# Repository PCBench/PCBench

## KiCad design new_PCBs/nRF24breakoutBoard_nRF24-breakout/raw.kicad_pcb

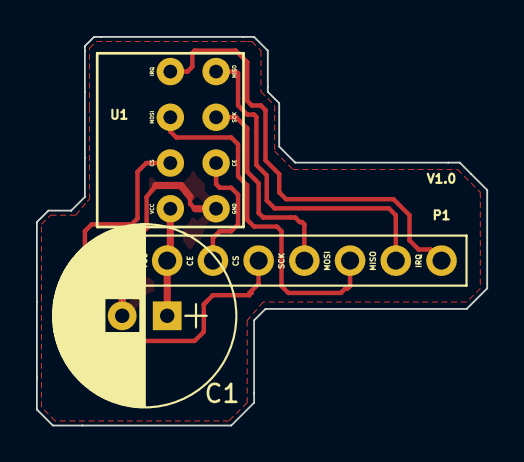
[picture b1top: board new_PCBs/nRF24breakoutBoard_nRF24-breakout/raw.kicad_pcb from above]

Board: 2 copper layers, 25.0 x 21.6 mm, 3 parts (0 on the bottom side), 8 nets.

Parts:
C1: 10uF; CP_Radial_D10.0mm_P2.50mm
P1: CONN_01X08; Pin_Header_Straight_1x08_Pitch2.54mm
U1: nRF24

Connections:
unnamed: C1.1, P1.2, U1.2
unnamed: C1.2, P1.1, U1.1
unnamed: P1.3, U1.3
unnamed: P1.4, U1.4
unnamed: P1.5, U1.5
unnamed: P1.6, U1.6
unnamed: P1.7, U1.7
unnamed: P1.8, U1.8

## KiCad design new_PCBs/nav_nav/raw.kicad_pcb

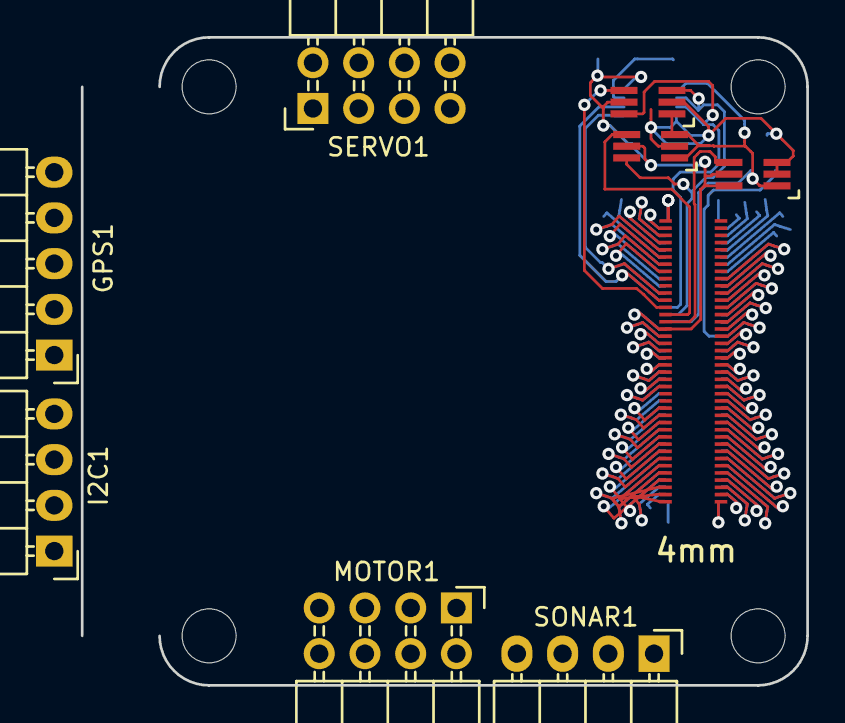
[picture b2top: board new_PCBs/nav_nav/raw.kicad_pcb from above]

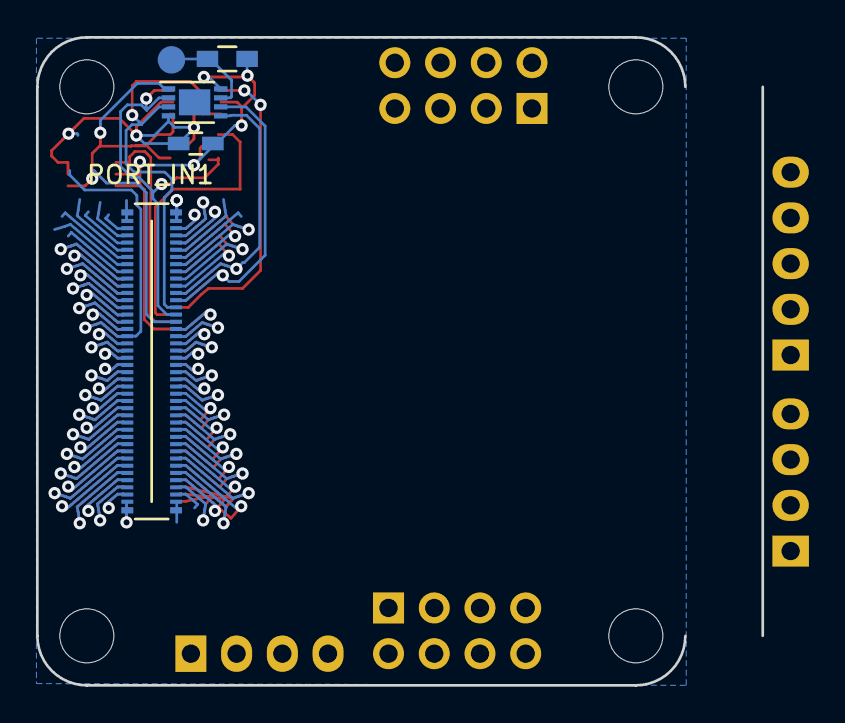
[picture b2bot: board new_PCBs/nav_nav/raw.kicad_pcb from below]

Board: 2 copper layers, 40.3 x 36.0 mm, 14 parts (5 on the bottom side), 62 nets.

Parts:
GPS1: CONN_01X05; Pin_Header_Angled_1x05
I2C1: CONN_01X04; Pin_Header_Angled_1x04
MOTOR1: CONN_02X04; Pin_Header_Angled_2x04
PORT_ANDOR1: SN74LVC1G0832; SC-70-6_Handsoldering
PORT_C1: 0.1uF; C_0603_HandSoldering
PORT_IC1: AT24CS02-MAHM; DFN-8-1EP_3x2mm_Pitch0.5mm
PORT_IN1: POLYSTACK_CONNECTOR; DF40-80pin-Header
PORT_INV1: SN74LVC1G58; SC-70-6_Handsoldering
PORT_OUT1: POLYSTACK_CONNECTOR; DF40-3-4mm-80pin-Receptacle
PORT_P1: CONN_01X01; Measurement_Point_Round-SMD-Pad_Small
PORT_R1: 10k; R_0603_HandSoldering
PORT_XOR1: SN74LVC1G58; SC-70-6_Handsoldering
SERVO1: CONN_02X04; Pin_Header_Angled_2x04
SONAR1: CONN_01X04; Pin_Header_Angled_1x04

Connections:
+5V: GPS1.1, I2C1.1, PORT_IN1.19, PORT_IN1.20, PORT_IN1.21, PORT_IN1.22, PORT_IN1.23, PORT_IN1.24, PORT_OUT1.19, PORT_OUT1.20, PORT_OUT1.21, PORT_OUT1.22, PORT_OUT1.23, PORT_OUT1.24, SONAR1.4
/ExpansionPort/3V3_0.3A_E: PORT_IN1.17, PORT_OUT1.17
/ExpansionPort/3V3_0.3A_LL: PORT_ANDOR1.5, PORT_C1.1, PORT_IC1.8, PORT_IN1.16, PORT_INV1.5, PORT_INV1.6, PORT_OUT1.16, PORT_R1.2, PORT_XOR1.5
/ExpansionPort/+BATT: PORT_IN1.18, PORT_OUT1.18
/ExpansionPort/ADC1: PORT_IN1.49, PORT_OUT1.49
/ExpansionPort/ADC2: PORT_IN1.50, PORT_OUT1.50
/ExpansionPort/BOOT: PORT_IN1.65, PORT_OUT1.65
/ExpansionPort/CAN_HI: PORT_IN1.67, PORT_OUT1.67
/ExpansionPort/CAN_LO: PORT_IN1.68, PORT_OUT1.68
/ExpansionPort/GPIO3: PORT_IN1.7, PORT_OUT1.5
/ExpansionPort/GPIO4: PORT_IN1.8, PORT_OUT1.6
/ExpansionPort/GPIO5: PORT_IN1.9, PORT_OUT1.7
/ExpansionPort/GPIO6: PORT_IN1.10, PORT_OUT1.8
/ExpansionPort/HEIGHT_1: PORT_ANDOR1.1, PORT_IC1.1, PORT_IN1.15, PORT_INV1.1, PORT_XOR1.1, PORT_XOR1.3
/ExpansionPort/HEIGHT_2: PORT_ANDOR1.3, PORT_IC1.2, PORT_IN1.14, PORT_XOR1.6
/ExpansionPort/HEIGHT_4: PORT_ANDOR1.6, PORT_IC1.3, PORT_IN1.13
/ExpansionPort/NEW_HEIGHT_1: PORT_INV1.4, PORT_OUT1.15
/ExpansionPort/NEW_HEIGHT_2: PORT_OUT1.14, PORT_XOR1.4
/ExpansionPort/NEW_HEIGHT_4: PORT_ANDOR1.4, PORT_OUT1.13
/ExpansionPort/RESET: PORT_IN1.66, PORT_OUT1.66
/ExpansionPort/SDMMC1_CK: PORT_IN1.55, PORT_OUT1.55
/ExpansionPort/SDMMC1_CMD: PORT_IN1.56, PORT_OUT1.56
/ExpansionPort/SDMMC1_D0: PORT_IN1.51, PORT_OUT1.51
/ExpansionPort/SDMMC1_D1: PORT_IN1.52, PORT_OUT1.52
/ExpansionPort/SDMMC1_D2: PORT_IN1.53, PORT_OUT1.53
/ExpansionPort/SDMMC1_D3: PORT_IN1.54, PORT_OUT1.54
/ExpansionPort/SPI1_MISO: PORT_IN1.79, PORT_OUT1.79
/ExpansionPort/SPI1_MOSI: PORT_IN1.80, PORT_OUT1.80
/ExpansionPort/SPI1_NSS: PORT_IN1.77, PORT_OUT1.77
/ExpansionPort/SPI1_SCK: PORT_IN1.78, PORT_OUT1.78
/ExpansionPort/SPI2_MISO: PORT_IN1.75, PORT_OUT1.75
/ExpansionPort/SPI2_MOSI: PORT_IN1.76, PORT_OUT1.76
/ExpansionPort/SPI2_NSS: PORT_IN1.73, PORT_OUT1.73
/ExpansionPort/SPI2_SCK: PORT_IN1.74, PORT_OUT1.74
/ExpansionPort/SPI3_MISO: PORT_IN1.71, PORT_OUT1.71
/ExpansionPort/SPI3_MOSI: PORT_IN1.72, PORT_OUT1.72
/ExpansionPort/SPI3_NSS: PORT_IN1.69, PORT_OUT1.69
/ExpansionPort/SPI3_SCK: PORT_IN1.70, PORT_OUT1.70
/ExpansionPort/TIM1: PORT_IN1.1, PORT_OUT1.1
/ExpansionPort/TIM2: PORT_IN1.2, PORT_OUT1.2
/ExpansionPort/TIM3: PORT_IN1.3, PORT_OUT1.3
/ExpansionPort/TIM4: PORT_IN1.4, PORT_OUT1.4
/ExpansionPort/UART1_RX: GPS1.3, PORT_IN1.40
/ExpansionPort/UART1_TX: GPS1.2, PORT_IN1.39
/ExpansionPort/UART2_RX: PORT_IN1.38, PORT_OUT1.40
/ExpansionPort/UART2_TX: PORT_IN1.37, PORT_OUT1.39
/ExpansionPort/UART3_RX: PORT_IN1.36, PORT_OUT1.38
/ExpansionPort/UART3_TX: PORT_IN1.35, PORT_OUT1.37
/ExpansionPort/UART4_RX: PORT_IN1.34, PORT_OUT1.36
/ExpansionPort/UART4_TX: PORT_IN1.33, PORT_OUT1.35
/ExpansionPort/UART5_RX: PORT_IN1.32, PORT_OUT1.34
/ExpansionPort/UART5_TX: PORT_IN1.31, PORT_OUT1.33
/ExpansionPort/UART6_RX: PORT_IN1.30, PORT_OUT1.32
/ExpansionPort/UART6_TX: PORT_IN1.29, PORT_OUT1.31
/ExpansionPort/UART7_RX: PORT_IN1.28, PORT_OUT1.30
/ExpansionPort/UART7_TX: PORT_IN1.27, PORT_OUT1.29
/ExpansionPort/UART8_RX: PORT_IN1.26, PORT_OUT1.28
/ExpansionPort/UART8_TX: PORT_IN1.25, PORT_OUT1.27
/ExpansionPort/i2c_SCL: I2C1.2, PORT_IN1.12, PORT_OUT1.12
/ExpansionPort/i2c_SDA: I2C1.3, PORT_IN1.11, PORT_OUT1.11
GND: GPS1.5, I2C1.4, PORT_ANDOR1.2, PORT_C1.2, PORT_IC1.4, PORT_IN1.57, PORT_IN1.58, PORT_IN1.59, PORT_IN1.60, PORT_IN1.61, PORT_IN1.62, PORT_IN1.63, PORT_IN1.64, PORT_INV1.2, PORT_INV1.3, PORT_OUT1.57, PORT_OUT1.58, PORT_OUT1.59, PORT_OUT1.60, PORT_OUT1.61, PORT_OUT1.62, PORT_OUT1.63, PORT_OUT1.64, PORT_XOR1.2, SONAR1.1
unnamed: PORT_IC1.7, PORT_P1.1, PORT_R1.1

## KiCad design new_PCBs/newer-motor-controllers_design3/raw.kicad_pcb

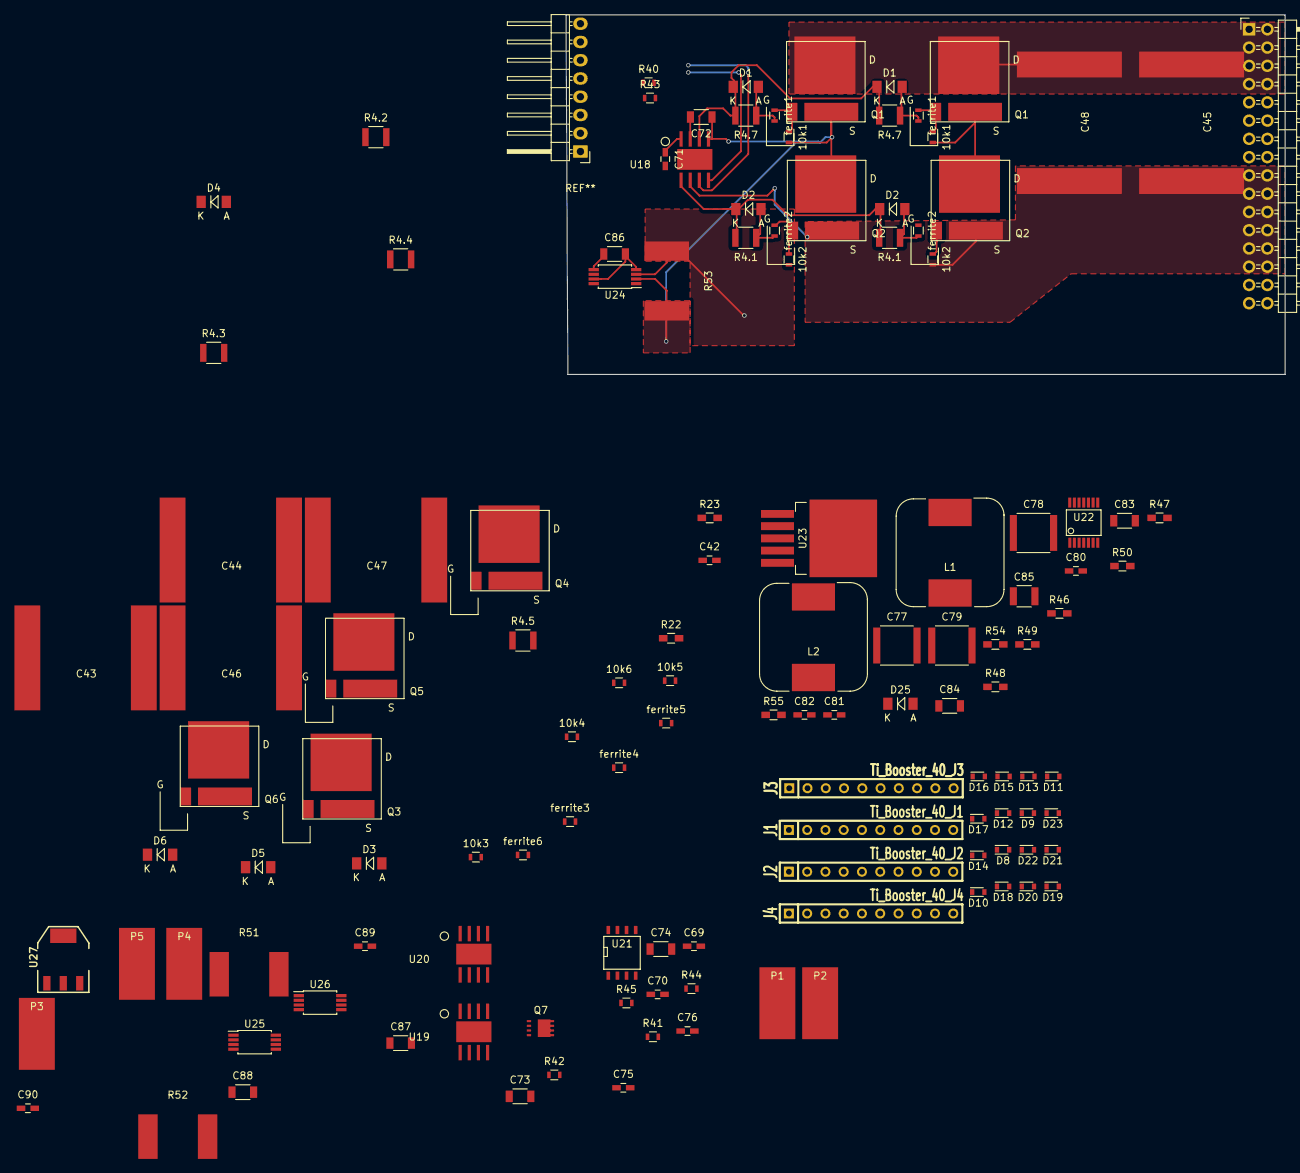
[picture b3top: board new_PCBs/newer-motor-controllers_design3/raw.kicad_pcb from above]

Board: 4 copper layers, 100.0 x 50.0 mm, 126 parts (0 on the bottom side), 59 nets.

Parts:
10k1, 10k1#2, 10k2, 10k2#2, 10k3, 10k4, 10k5, 10k6: R_Small; R_0603
C42: 2.2uf; C_0603_HandSoldering
C43, C44, C45, C46, C47, C48: 4.7uf; cap_6065
C69, C70, C71, C82, C89: 1uf; C_0603_HandSoldering
C72, C73, C74, C86, C87, C88: 0.1uf; C_1206
C75: 0.1uf; C_0603_HandSoldering
C76: 10pf; C_0603_HandSoldering
C77, C78, C79: 1uf 250V; C_2220
C80: 22nf; C_0603_HandSoldering
C81: 10nf; C_0603_HandSoldering
C83, C84: 10uf; C_1206
C85: 100uf; C_1210
C90: 10uf; C_0603_HandSoldering
D1, D1#2, D2, D2#2, D3, D4, D5, D6: D_Schottky_Small; MiniMELF_Standard
D8, D9, D10, D11, D12, D13, D14, D15, D16, D17, D18, D19, D20, D21, D22, D23: TVS; D_0603
D25: D_Schottky; MiniMELF_Standard
J1: Ti_Booster_40_J1; SIL-10J1
J2: Ti_Booster_40_J2; SIL-10J2
J3: Ti_Booster_40_J3; SIL-10J3
J4: Ti_Booster_40_J4; SIL-10J4
L1, L2: INDUCTOR; MSS1583-154KED
P1: V-; SolderWirePad_single_SMD_5x10mm
P2: V+; SolderWirePad_single_SMD_5x10mm
P3: motor_C; SolderWirePad_single_SMD_5x10mm
P4: motor_B; SolderWirePad_single_SMD_5x10mm
P5: motor_A; SolderWirePad_single_SMD_5x10mm
Q1, Q1#2, Q2, Q2#2, Q3, Q4, Q5, Q6: FDMT-800; P-PG-HSOF-08
Q7: Q_NMOS_DSG; VSONP-8
R4.1, R4.1#2, R4.2, R4.3, R4.4, R4.5, R4.7, R4.7#2: R_Small; R_1210
R22: NTC 10k; R_0603_HandSoldering
R23: 10k; R_0603_HandSoldering
R40, R41, R42: 1.8K; R_0603
R43, R44, R45: 39K; R_0603
R46: 75k; R_0603_HandSoldering
R47: 4.42k; R_0603_HandSoldering
R48: 499k; R_0603_HandSoldering
R49: 13k; R_0603_HandSoldering
R50: 2k; R_0603_HandSoldering
R51, R52, R53: 0.001R; SHUNT_CSS2H-3920
R54: 1.8K; R_0603_HandSoldering
R55: 39K; R_0603_HandSoldering
U18, U19, U20: UCC27210; SO_PowerPAD-8
U21: Si8751; SOIC-8-N
U22: LM5161; SSOP-14
U23: LM2595; TO-263-5Lead
U24, U25, U26: INA240; TSSOP-8_4.4x3mm_Pitch0.65mm
U27: NCP1117ST33T3G; SOT-223
ferrite1, ferrite1#2, ferrite2, ferrite2#2, ferrite3, ferrite4, ferrite5, ferrite6: R_Small; R_0603

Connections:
+3V3: D9.1, J1.1, R22.1
+5V: C75.1, C85.1, C90.1, J3.1, L2.2, U21.1, U23.4, U27.3
+15V: C76.1, C83.1, C84.1, L1.2, Q7.1, R49.1, U23.2
/Ti_120vgate/EN_GATE: D10.1, J2.8, U21.3
/Ti_120vgate/H1: D1.1, D1#2.1, R4.7.2, R4.7#2.2, U18.3
/Ti_120vgate/H2: D3.1, R4.2.2, U19.3
/Ti_120vgate/H3: D5.1, R4.4.2, U20.3
/Ti_120vgate/L1: D2.1, D2#2.1, R4.1.2, R4.1#2.2, U18.8
/Ti_120vgate/L2: D4.1, R4.3.2, U19.8
/Ti_120vgate/L3: D6.1, R4.5.2, U20.8
/Ti_120vgate/PWM_H1: D18.1, J4.1, U18.5
/Ti_120vgate/PWM_H2: D20.1, J4.3, U19.5
/Ti_120vgate/PWM_H3: D22.1, J4.5, U20.5
/Ti_120vgate/PWM_L1: D19.1, J4.2, U18.6
/Ti_120vgate/PWM_L2: D21.1, J4.4, U19.6
/Ti_120vgate/PWM_L3: D23.1, J4.6, U20.6
/Ti_120vgate/phase_a_in: 10k1.2, 10k1#2.2, C72.1, Q1.2, Q1#2.2, Q2.1, Q2#2.1, R43.1, R53.2, U18.4, U24.2
/Ti_120vgate/phase_b_in: 10k3.2, C73.1, Q3.2, Q4.1, R44.1, R52.2, U19.4, U25.2
/Ti_120vgate/phase_c_in: 10k5.2, C74.1, Q5.2, Q6.1, R45.1, R51.2, U20.4, U26.2
/connector/CurrentA: D15.1, J3.7, U24.8
/connector/CurrentB: D16.1, J3.8, U25.8
/connector/CurrentC: D17.1, J3.9, U26.8
/connector/TEMP: C42.1, D8.1, J2.3, R22.2, R23.1
/connector/VBUS_sense: D11.1, J3.3, R54.1, R55.2
/connector/Vsense_a: D12.1, J3.4, R40.2, R43.2
/connector/Vsense_b: D13.1, J3.5, R41.2, R44.2
/connector/Vsense_c: D14.1, J3.6, R42.2, R45.2
/mosfet/VBUS: C43.2, C44.2, C45.2, C46.2, C47.2, C48.2, C77.1, C78.1, C79.1, P2.1, Q1.1, Q1#2.1, Q3.1, Q5.1, R46.1, R48.2, R55.1, U22.3
GND: 10k2.2, 10k2#2.2, 10k4.2, 10k6.2, C42.2, C43.1, C44.1, C45.1, C46.1, C47.1, C48.1, C69.2, C70.2, C71.2, C75.2, C77.2, C78.2, C79.2, C80.2, C82.2, C83.2, C84.2, C85.2, C86.2, C87.2, C88.2, C89.2, C90.2, D8.2, D9.2, D10.2, D11.2, D12.2, D13.2, D14.2, D15.2, D16.2, D17.2, D18.2, D19.2, D20.2, D21.2, D22.2, D23.2, D25.2, J2.1, J3.2, P1.1, Q2.2, Q2#2.2, Q4.2, Q6.2, R23.2, R40.1, R41.1, R42.1, R47.2, R50.2, R54.2, U18.7, U19.7, U20.7, U21.4, U22.1, U22.2, U22.8, U23.3, U24.4, U24.7, U25.4, U25.7, U26.4, U26.7, U27.1
unnamed: 10k1.1, 10k1#2.1, Q1.3, Q1#2.3, ferrite1.1, ferrite1#2.1
unnamed: 10k2.1, 10k2#2.1, Q2.3, Q2#2.3, ferrite2.1, ferrite2#2.1
unnamed: 10k3.1, Q3.3, ferrite3.1
unnamed: 10k4.1, Q4.3, ferrite4.1
unnamed: 10k5.1, Q5.3, ferrite5.1
unnamed: 10k6.1, Q6.3, ferrite6.1
unnamed: C69.1, C70.1, C71.1, Q7.2, U18.1, U19.1, U20.1, U21.5
unnamed: C72.2, U18.2
unnamed: C73.2, U19.2
unnamed: C74.2, U20.2
unnamed: C76.2, U21.7
unnamed: C80.1, U22.6
unnamed: C81.1, L1.1, U22.12, U22.13, U22.14
unnamed: C81.2, U22.11
unnamed: C82.1, U22.10
unnamed: C86.1, C87.1, C88.1, C89.1, U24.5, U24.6, U25.5, U25.6, U26.5, U26.6, U27.2
unnamed: D1.2, D1#2.2, R4.7.1, R4.7#2.1, ferrite1.2, ferrite1#2.2
unnamed: D2.2, D2#2.2, R4.1.1, R4.1#2.1, ferrite2.2, ferrite2#2.2
unnamed: D3.2, R4.2.1, ferrite3.2
unnamed: D4.2, R4.3.1, ferrite4.2
unnamed: D5.2, R4.4.1, ferrite5.2
unnamed: D6.2, R4.5.1, ferrite6.2
unnamed: D25.1, L2.1, U23.1
unnamed: P3.1, R51.1, U26.3
unnamed: P4.1, R52.1, U25.3
unnamed: P5.1, R53.1, U24.3
unnamed: Q7.3, U21.8
unnamed: R46.2, R47.1, U22.4
unnamed: R48.1, U22.5
unnamed: R49.2, R50.1, U22.9

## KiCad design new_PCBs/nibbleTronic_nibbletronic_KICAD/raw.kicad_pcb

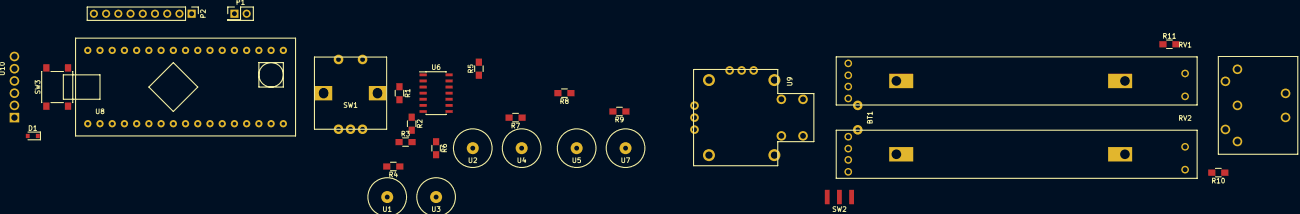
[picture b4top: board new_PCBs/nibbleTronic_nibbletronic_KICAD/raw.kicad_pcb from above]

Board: 2 copper layers, 31 parts (0 on the bottom side), 40 nets, no tracks yet.

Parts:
BT1: Battery; 9V_BATTERY_CLIP
D1: D; D_0805
P1: CONN_01X02; Pin_Header_Straight_2x01_Pitch2.54mm
P2: CONN_01X09; Pin_Header_Straight_1x09_Pitch2.54mm
P3: DIN_5; HIRSCHMANN_MAB_5
R1, R3: 4.7k; R_0805_HandSoldering
R2: 47k; R_0805_HandSoldering
R4, R5, R6, R7, R8, R9: 10k; R_0805_HandSoldering
R10, R11: 220; R_0805_HandSoldering
RV1, RV2: 10k; ALPS_402125
SW1: Rotary_Encoder_Switch; ALPS-STEC12E
SW2: Switch_SPDT_x2; ESP40XX
SW3: SW_PUSH; SW_SPST_PTS645
U1, U2, U3, U4, U5, U7: Pad
U6: AT_42QT1070-SSU; SOIC-14_3.9x8.7mm_Pitch1.27mm
U8: Arduino_micro; ARDU_MICRO_SOCKET
U9: Joystick; ALPS_RKJXP
U10: MPX5010DP

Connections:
/3V3: P2.4, U8.2
/5V: P2.3, R1.2, R2.2, R3.2, R11.1, U6.1, U6.4, U8.12, U10.3
/A1: P2.9, U8.5
/D4: P2.5, U8.26
/D5: P2.6, U8.27
/D8: P2.7, U8.30
/D13: P2.8, U8.1
/REF: P2.2, RV1.3, RV2.3, SW3.2, U8.3, U9.3, U9.6
/SCL: P1.1, R3.1, U6.6, U8.25
/SDA: P1.2, R1.1, U6.3, U8.24
GND: BT1.2, P2.1, P3.2, RV1.1, RV2.1, SW1.5, U6.2, U6.14, U8.14, U8.23, U9.1, U9.4, U9.8, U10.2
unnamed: BT1.1, SW2.3
unnamed: D1.1, SW3.1, U8.4
unnamed: D1.2, U10.1
unnamed: P3.4, R11.2
unnamed: P3.5, R10.1
unnamed: R2.1, U6.5, U8.29
unnamed: R4.1, U6.7
unnamed: R4.2, U1.1
unnamed: R5.1, U2.1
unnamed: R5.2, U6.13
unnamed: R6.1, U6.8
unnamed: R6.2, U3.1
unnamed: R7.1, U4.1
unnamed: R7.2, U6.12
unnamed: R8.1, U5.1
unnamed: R8.2, U6.11
unnamed: R9.1, U7.1
unnamed: R9.2, U6.10
unnamed: R10.2, U8.20
unnamed: RV1.2, U8.8
unnamed: RV2.2, U8.9
unnamed: SW1.1, U8.32
unnamed: SW1.2, U8.33
unnamed: SW1.3, U8.34
unnamed: SW1.4, U8.31
unnamed: SW2.2, U8.15
unnamed: U8.6, U9.2
unnamed: U8.7, U9.5
unnamed: U8.28, U9.7
